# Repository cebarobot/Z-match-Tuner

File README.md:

# Z-match Tuner
> An open source Z-match Tuner for QRP  
> 一个开源的用于 QRP 的 Z-match 天调

## File List 文件列表
* `Z-match manual.pdf` 中文说明书
* `Z-match chematic.pdf ` 原理图
* `z-match-2.zip` KiCad 工程文件
* `z-match-2-gerber.zip` Gerber 制板文件
* `z-match panel.eprj` 前后面板的 LCEDA 工程文件

## License
MIT LICENSE

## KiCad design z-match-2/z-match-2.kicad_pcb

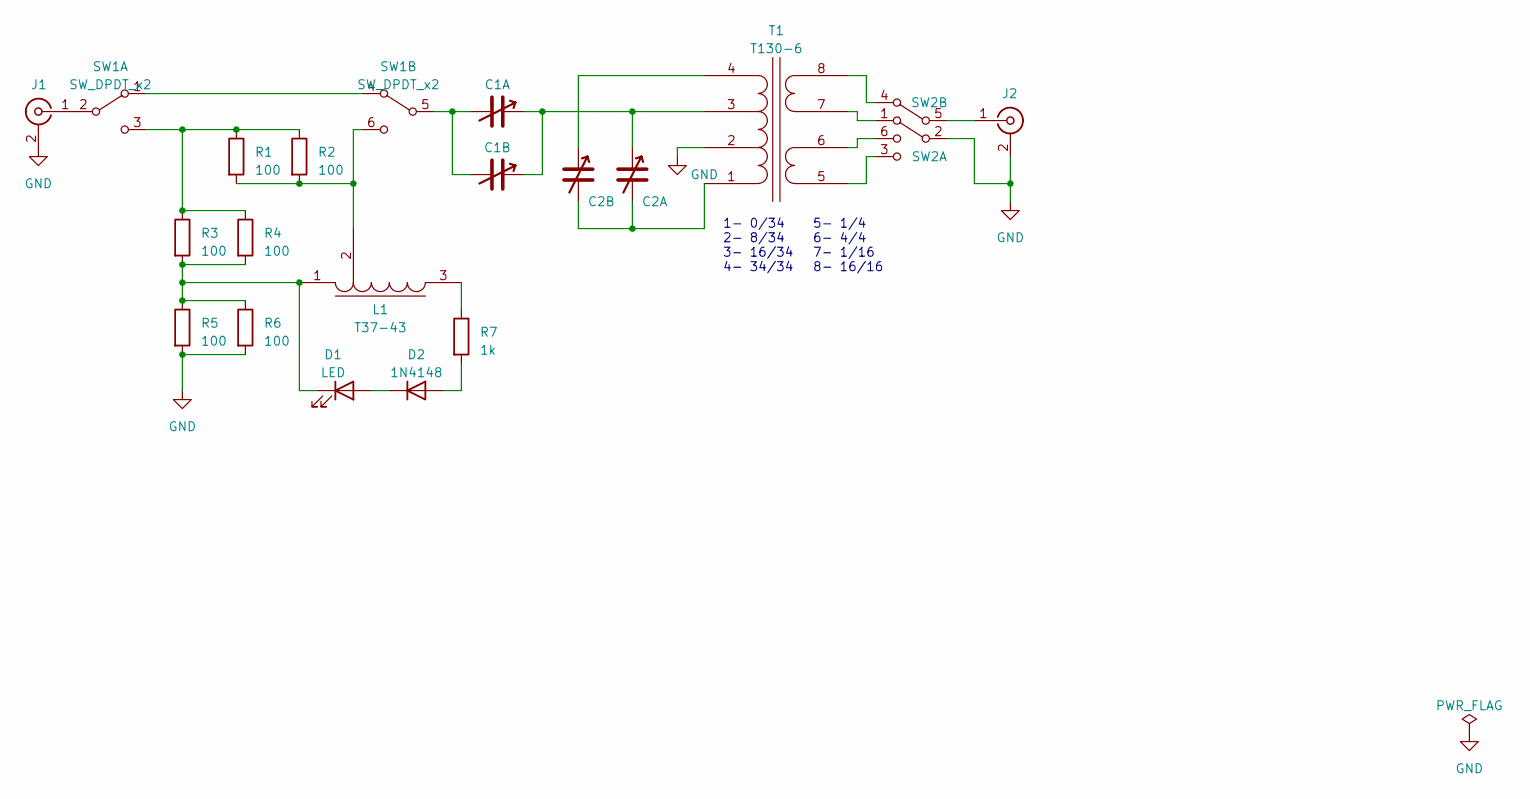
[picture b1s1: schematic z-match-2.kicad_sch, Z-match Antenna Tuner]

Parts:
C1, C2: CBM_Main; CBM-4443BF-1AB4-Vertical
D1: LED; LED_D3.0mm
D2: 1N4148; D_DO-35_SOD27_P7.62mm_Horizontal
J1, J2: Conn_Coaxial; BNC-KWE29X16
L1: T37-43
R1, R2, R3, R4, R5, R6: 100; R_Axial_DIN0414_L11.9mm_D4.5mm_P15.24mm_Horizontal
R7: 1k; R_Axial_DIN0207_L6.3mm_D2.5mm_P10.16mm_Horizontal
SW1, SW2: SW_DPDT_x2; MT-0-202-A003-M003-RS-MODEL
T1: T130-6

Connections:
GND: J1.2 (Ext), J2.2 (Ext), R5.2, R6.2, SW2.2 (B), T1.2 (A2)
unnamed: D1.2 (A), D2.1 (K)
unnamed: D1.1 (K), L1.1, R3.2, R4.2, R5.1, R6.1
unnamed: D2.2 (A), R7.2
unnamed: J1.1 (In), SW1.2 (B)
unnamed: J2.1 (In), SW2.5 (B)
unnamed: L1.3, R7.1
unnamed: SW1.1 (A), SW1.4 (A)
unnamed: R1.1, R2.1, R3.1, R4.1, SW1.3 (C)
unnamed: C1.1, SW1.5 (B)
unnamed: L1.2, R1.2, R2.2, SW1.6 (C)
unnamed: SW2.1 (A), T1.7 (C1)
unnamed: SW2.3 (C), T1.5 (B1)
unnamed: SW2.4 (A), T1.8 (C2)
unnamed: SW2.6 (C), T1.6 (B2)
unnamed: C2.1, T1.1 (A1)
unnamed: C1.2, C1.3, C2.2, T1.3 (A3)
unnamed: C2.3, T1.4 (A4)

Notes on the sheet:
5- 1/4 6- 4/4 7- 1/16 8- 16/16
1- 0/34 2- 8/34 3- 16/34 4- 34/34

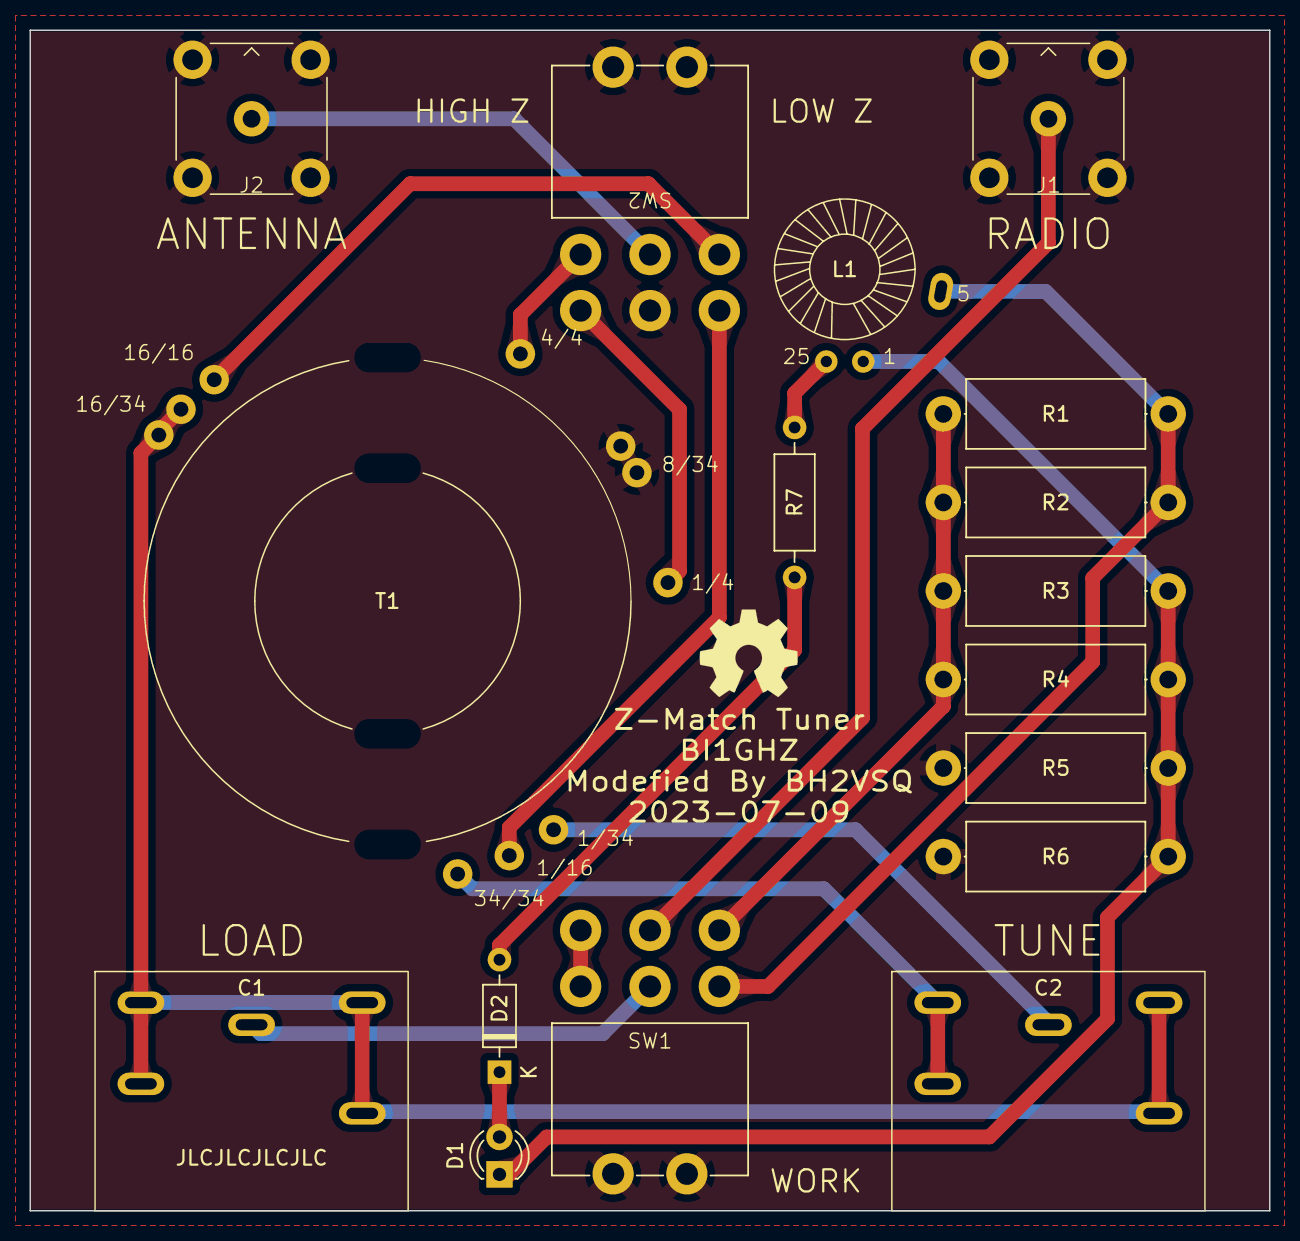
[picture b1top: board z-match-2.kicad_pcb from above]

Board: 2 copper layers, 84.0 x 80.0 mm, 17 parts (0 on the bottom side), 18 nets.

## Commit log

2023-04-12 Create LICENSE
2023-07-09 Modified PCB file
